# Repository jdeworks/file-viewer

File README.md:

# File Viewer

**v0.1.0 Public beta**

File Viewer is a private, browser-based file workbench for opening, inspecting, comparing, and editing files without first sending them to a hosted service.

**[Open File Viewer](https://jdeworks.github.io/file-viewer/)**

## Why File Viewer

Open a file, a folder, or pasted text in a browser workspace that adapts to the content. Read source beside a rendered preview, inspect metadata, make an edit, compare revisions, and download the result. On phones, source and preview remain usable as separate tabs.

The public beta is for people who need a practical local-first viewer before reaching for a desktop application, an upload site, or a one-off conversion tool.

## Privacy and network modes

File Viewer has different network behavior depending on the mode you choose:

| Mode | What to expect |
| --- | --- |
| Browser mode (default) | By default, app requests stay on the app's own origin. The normal browser workflow is designed without file uploads, accounts, analytics, telemetry, or runtime CDN dependencies. |
| Documents with external resources | Eager off-origin resources in Markdown, safe HTML, SVG, email, and EPUB previews are blocked by default. Ordinary links remain user-initiated; a blocked Markdown image exposes a labelled source link that states it will request that exact URL in a new tab. |
| HTML dependency presets | Selecting Bootstrap or Tailwind makes no request. **Load** opens a separate confirmation listing every exact CSS/JavaScript URL; uncached resources use credential-free, no-referrer CORS GETs and successful responses may enter the dedicated dependency cache. |
| Confirmed script-enabled HTML | HTML previews are sanitized by default. The raw-document confirmation explains that trusted HTML can request images, styles, fonts, media, frames, form targets, and URLs computed by JavaScript. It remains in an opaque-origin script sandbox, but its network behavior is controlled by the document. |
| Optional Companion | The desktop Companion is opt-in. When enabled, the browser exchanges selected file paths and bytes with its local service at `127.0.0.1` for watched-folder workflows and save-back. |

Browser developer tools remain the best way to inspect requests for your browser, deployment, and selected file. The viewer is designed so ordinary file handling stays in the tab; external references are not the same as uploading the opened file, but they can still disclose normal request metadata to their destination.

## Everyday workflows

- Open individual files, folders, drag-and-drop content, or paste text.
- Read raw source, a rendered preview, or both side by side; use mobile tabs when space is tight.
- Edit supported text formats, format documents, and download your changes.
- Compare original and current content with standard or move-aware diffs.
- Browse a folder tree, inspect file metadata, search content, and export edited work.
- Capture supported rendered previews as PNGs.

## Formats

File Viewer currently covers **140+ base types** plus hundreds of recognized developer/config files. Detection is intentionally broad, while rendering depth varies by format and browser.

Curated categories include:

- Documents and books: Markdown, HTML, PDF, EPUB, FB2, DOCX, ODT, PPTX, and RTF.
- Data and structured text: JSON, CSV, YAML, TOML, XML, INI, SQL, GeoJSON, GPX, calendars, and contacts.
- Code and configuration: common source languages plus project, editor, CI, package-manager, infrastructure, and operating-system configuration files.
- Media and images: common raster, vector, audio, video, subtitle, and font formats.
- Office, archives, binaries, 3D, and scientific formats: spreadsheets, presentations, ZIP-family containers, SQLite, 3D models, and selected specialist files.

Use the built-in examples to see the current presentation for a specific format. Some advanced formats and codecs depend on the browser and may offer inspection or download rather than a complete preview.

Search-friendly details for common formats are published in the [format guide](https://jdeworks.github.io/file-viewer/formats/). The main URL still opens the full-screen tool directly; the guides are optional reference pages, not an introductory flow.

## Offline use

No installation is required. File Viewer uses a browser-mode web app manifest and a service worker, not an install-first application flow.

- **Cache on use:** assets fetched while you work can remain available for later offline use.
- **Save offline bundles:** choose bundles from the in-app **Save offline** control when you want a more deliberate offline set.
- **Optional heavy packages:** larger viewers and examples are selectable, so a full offline bundle does not have to be the starting point.

An offline preview can be unavailable when its renderer was not previously cached. Reconnect once, open the needed feature, or save an appropriate offline bundle before going offline.

## Optional Companion

The browser app is useful on its own. The optional [Companion](companion/README.md) adds local watched folders, save-back, file-change watching, and native folder selection where supported. It runs a local service on `127.0.0.1` and requires an explicit browser opt-in.

Release builds may be unsigned while the project establishes its distribution process. Treat operating-system and browser warnings as a prompt to verify the release source and checksum; checksums help verify downloaded bytes, but do not establish publisher identity. See [Releases](https://github.com/jdeworks/file-viewer/releases) for published artifacts and [Issues](https://github.com/jdeworks/file-viewer/issues) for beta feedback.

## Beta notes

Core workflows are ready for broad testing; advanced format support is still improving. Please report a reproducible file type, browser/version, and expected versus observed behavior in [Issues](https://github.com/jdeworks/file-viewer/issues).

- Automated coverage targets Chromium. Firefox and Safari are best-effort targets.
- Media codecs and advanced-format behavior can vary by browser, operating system, and available decoding support.
- Non-media files over 64 MiB are read as a bounded head for browsing instead of fully loaded into memory. Formats that require the complete file may not render from that bounded head. Large audio and video may stream from the browser's file handle instead.

## Develop

File Viewer is a static client application served from `docs/`:

```sh
cd docs
python3 -m http.server 8000
# http://localhost:8000
```

Core orchestration lives in `docs/core/`; file-type modules live in `docs/types/<id>/`; runtime libraries are vendored in `docs/vendor/`. To add a type, create its module folder and register it in `docs/core/registry.js`. Keep runtime dependencies local to the repository rather than adding a CDN.

### Search metadata

Indexable pages and their canonical metadata are declared in `seo.config.json`. Visible guide copy remains hand-authored; the generator owns only each marker-delimited head block and `docs/sitemap.xml`.

```sh
node scripts/seo.mjs --write  # regenerate metadata and sitemap after editing the config
node scripts/seo.mjs --check  # validate metadata, H1s, static links, and sitemap freshness
```

The deployed sitemap is submitted through a Google Search Console URL-prefix property for `https://jdeworks.github.io/file-viewer/`. Search Console verification uses a static token supplied by the site owner and does not add analytics or visitor-side code.

## Test

```sh
node tests/movediff.test.mjs
node tests/smoke.mjs
./scripts/check.sh --fast     # routine pre-push gate (scoped, ~minutes)
./scripts/check.sh            # RELEASE gate (~7 min): core smoke + representative samples
./scripts/check.sh --exhaustive   # open-EVERYTHING sweep (on command, ≤30 min)
```

The smoke test serves the app and drives Chromium while checking for unexpected off-origin requests in the default browser mode. The gate has three modes: `--fast` for every push, bare `./scripts/check.sh` as the release gate, and `--exhaustive` for the full open-everything sweep (add `--dry-run` to any mode to print its selection without launching a browser).

To verify the real static host negotiates compression after a deployment, run:

```sh
node scripts/check-deployed-compression.mjs
# or: node scripts/check-deployed-compression.mjs https://example.test/file-viewer/
```

This checks representative JavaScript and CSS responses for `Content-Encoding: br|gzip` and
`Vary: Accept-Encoding`. The repository deliberately does not treat nearby `.gz` or `.br` files
as proof of compression because a static host must be configured to serve the matching headers.

## License

[MIT](LICENSE). Vendored packages retain their own licenses; pinned versions are recorded in
[`docs/vendor/VERSIONS.json`](docs/vendor/VERSIONS.json).

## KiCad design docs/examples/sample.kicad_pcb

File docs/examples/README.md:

# Example fixture policy

`index.json` is the shipped sample catalog and `compatibility.json` records the completed capability and fixture-quality audit for every registered type and enhanced known-file view. Matrix version 3 is generated from the live registries and catalog; every row is marked `auditStatus: "validated"` and must name at least one fixture that really selects that base or enhanced viewer.

Run `node scripts/audit-example-catalog.mjs` to verify catalog files, declared detector results, concrete enhanced-view IDs, and provenance triples. `--fix` normalizes legacy enhanced markers to the viewer the real detector selects. Run `node scripts/gen-example-compatibility.mjs` after registry or catalog changes, then `node tests/example-compatibility.test.mjs` to enforce the full matrix.

## Generating fixtures

Simple structured and text examples stay as reviewed source files. The project does not expose a sample-generator UI and does not maintain a generic local generator: such a generator would mostly reproduce short files that are easier to understand, review, and vary directly, while adding another user surface and schema to maintain.

Formats that require exact binary layout, checksums, media encoding, or container structure use narrow deterministic scripts named `scripts/gen-sample-*`. A generator should state how to run it, avoid network access, produce byte-for-byte stable output, and have a focused structural or renderer test. This keeps complicated fixture construction reproducible without turning generation into a product feature.

Repository-authored fixtures inherit the repository license and are identified by the absence of external `source` metadata. External or derived assets must carry all three catalog fields: `source`, `license`, and `attribution`. A partial provenance record is invalid.

License names in the catalog describe the terms checked at promotion time. Sources are pinned to a specific upstream file or release where possible; copyright notices required by permissive binary licenses are preserved in the corresponding `attribution` field. A source page without an explicit redistribution grant is not a license.

## Promoting external samples

Do not add an external download directly to `index.json`. FileExamples.com slugs in the compatibility matrix are discovery hints, not an approval or download mechanism. First verify that a candidate's license permits redistribution, record its origin and any derivation, inspect it for secrets or personal data, validate detection and rendering offline, and add focused coverage for the behavior it is meant to exercise. Unvetted downloads stay outside the shipped catalog.

Every indexed sample is exercised by the exhaustive examples-catalog lane. When a catalog sample exposes a parser failure, reduce that failure to the smallest representative focused fixture before changing the parser; keep the catalog file as end-to-end coverage when redistribution remains safe.

The catalog deliberately includes broad programming-language coverage, binary/container and 3D fixtures with structural tests, locally unlockable password-protected PDF, SQLCipher-v4 SQLite, and ZIP fixtures, three explicit malformed text/data fixtures, and a self-contained semantic HTML theme showcase exercised in light and dark mode. These are maintained as representative quality lanes; adding arbitrary volume is not a substitute for a focused detector/parser assertion.

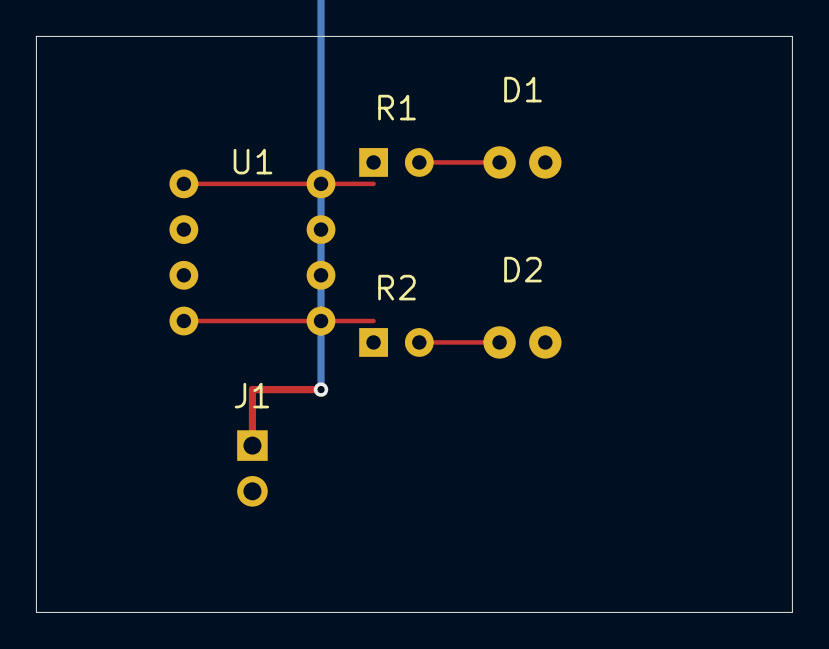
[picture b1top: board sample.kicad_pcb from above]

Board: 2 copper layers, 42.0 x 32.0 mm, 6 parts (0 on the bottom side), 6 nets.

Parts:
D1: LED_Red; LED_D5.0mm
D2: LED_Green; LED_D5.0mm
J1: PWR; PinHeader_1x02_P2.54mm_Vertical
R1, R2: 330R; R
U1: ATtiny85; DIP-8_W7.62mm

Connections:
/PB0: R1.1, U1.2, U1.7
/PB1: R2.1, U1.3, U1.6
GND: D1.2, D2.2, J1.2, U1.4
LED1_A: D1.1, R1.2
LED2_A: D2.1, R2.2
VCC: J1.1, U1.5, U1.8
